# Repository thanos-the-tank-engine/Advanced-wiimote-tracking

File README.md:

# Advanced-wiimote-tracking
A python application for tracking nintendo wii controllers in 6 degrees of freedom

**This project is still very much a WIP. very little functionality has been implemented in it, and it is nowhere near completion at this time**

This application is designed to allow you to connect wii controllers to a computer and then channel the inputs from it into various emulated HID devices.
The goal of this software is to reduce the barrier of entry for 6DOF controller systems by enabling the use of a relatively low-cost system that can easily be DIY'd out of readily available objects. most current methods, such as the 3d-mouse style of controller, or the controllers used for a VR headset, are incredibly expensive. this software will allow you to accomplish the same thing using something that you probably have lying around already, or can buy secondhand for very little cost if you don't.

Included in this repository:  
\> Python scripts
\> KiCad project containing PCB layout and schematic for an improved sensor bar that expands on the capabilities of the Wii controller by enabling true 6DOF tracking.  
\> 3D model for the optional case of the improved sensor bar

Will be included in the future  
\> Firmware for improved sensor bar  
\> Maybe windows compatibility, if you windows-using plebians get lucky  

#Setup  
Right now, none of the setup process is automated. this means you will have to do it all yourself.
You will need to install my modified version of the Cwiid library that has support for the balance board added to it.
you will have to compile it yourself. I have not bothered trying to run this outside of my IDE because none of the UI exists yet.
If you want to use this on its own, good luck with that. either wait until it's finished or finish it yourself.

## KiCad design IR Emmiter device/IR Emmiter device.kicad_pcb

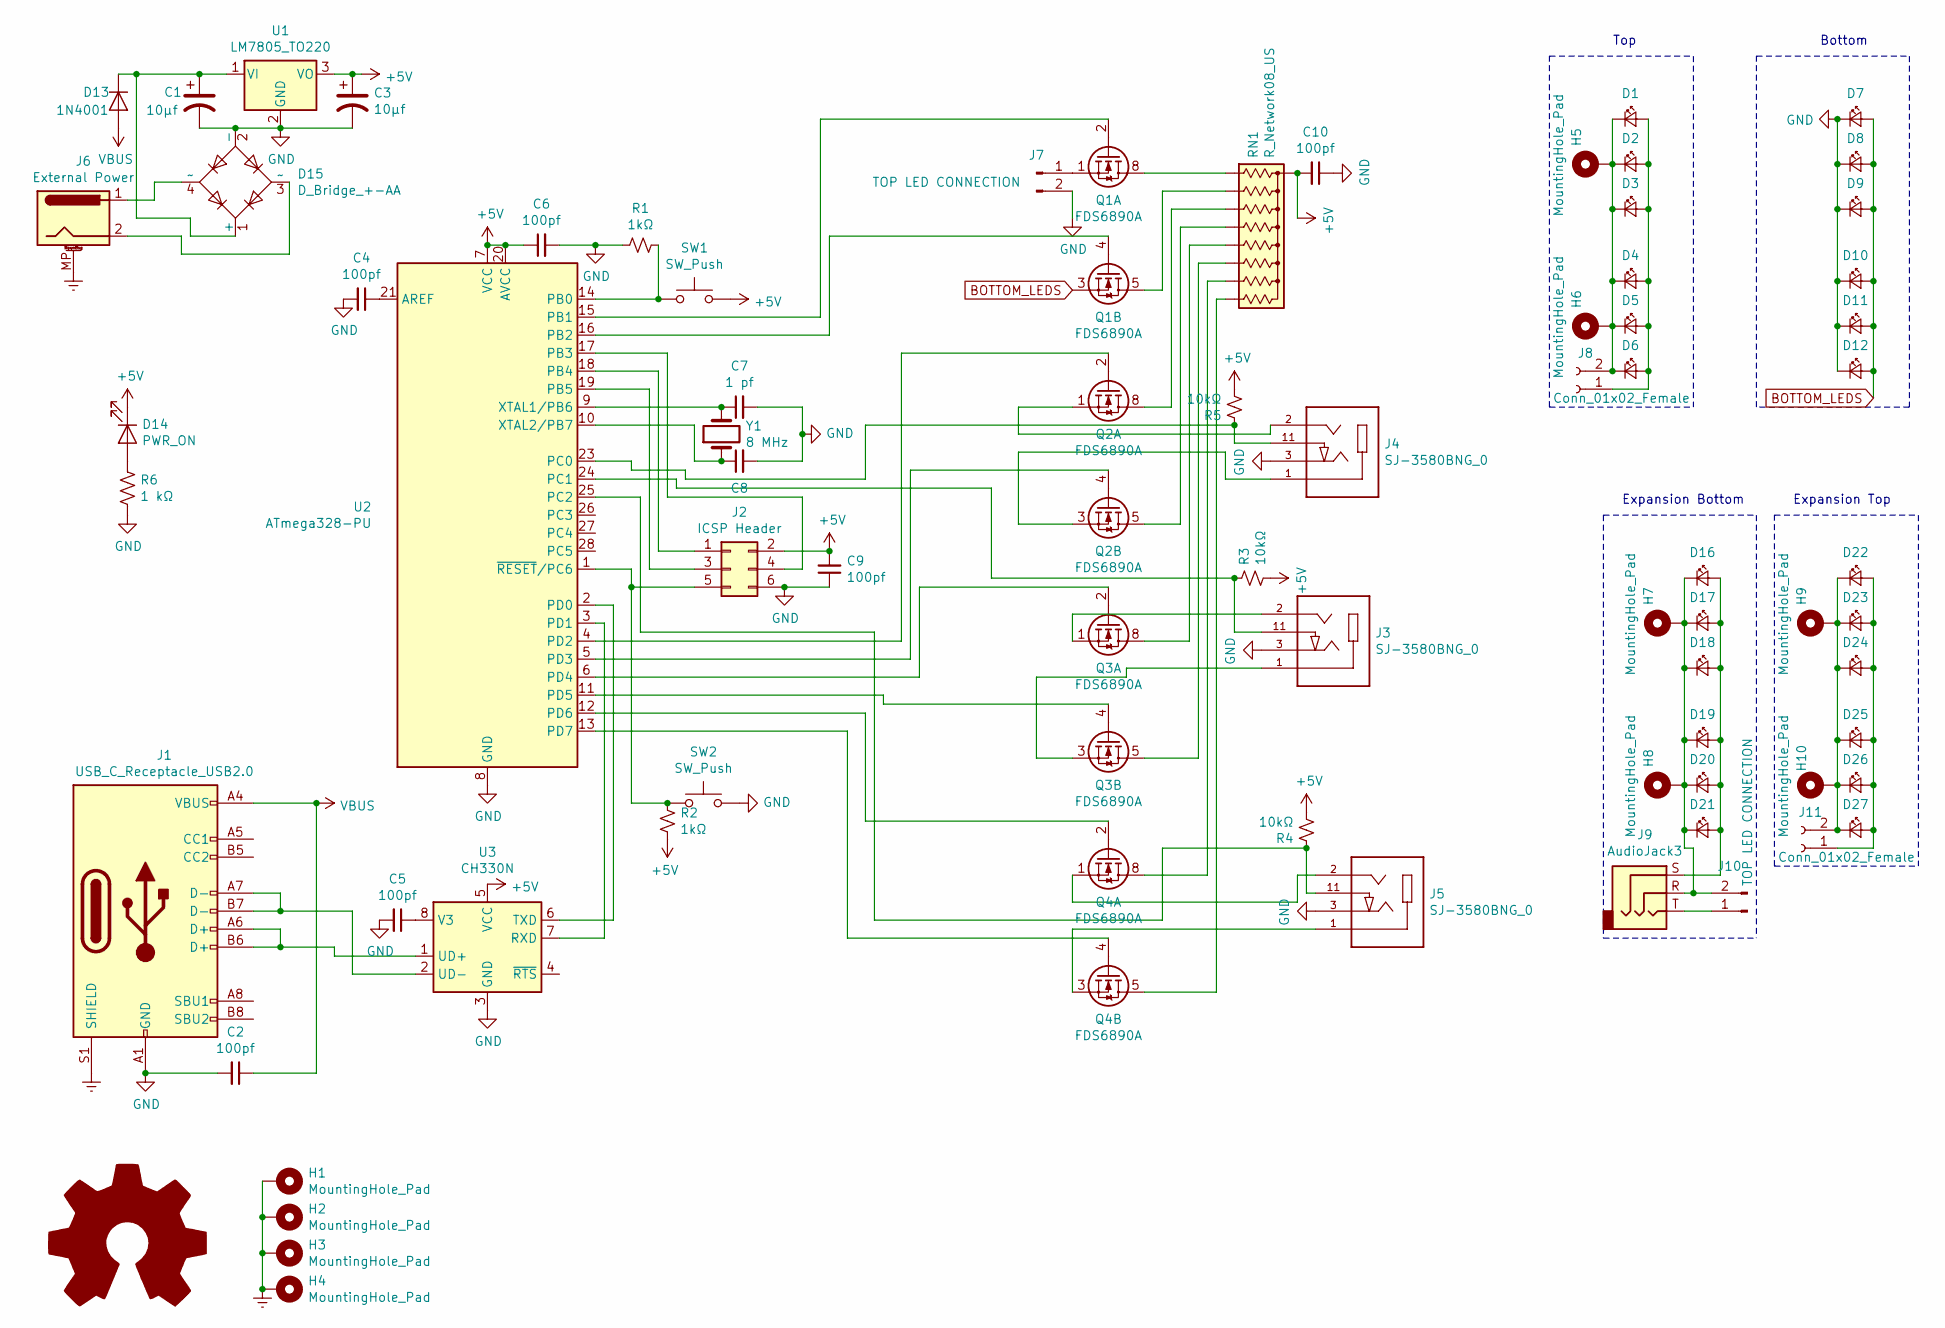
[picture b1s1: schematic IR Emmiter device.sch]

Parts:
C1, C3: 10μf; CP_Radial_D8.0mm_P2.50mm
C2, C4, C5, C6, C9, C10: 100pf; C_Disc_D8.0mm_W5.0mm_P10.00mm
C7: 1 pf; C_Disc_D8.0mm_W5.0mm_P10.00mm
C8: 1pf; C_Disc_D8.0mm_W5.0mm_P10.00mm
D1, D2, D3, D4, D5, D6, D7, D8, D9, D10, D11, D12, D16, D17, D18, D19, D20, D21, D22, D23, D24, D25, D26, D27: LED_Small; LED_D5.0mm_Horizontal_O1.27mm_Z3.0mm_Clear
D13: 1N4001; D_DO-41_SOD81_P10.16mm_Horizontal
D14: PWR_ON; LED_D5.0mm_Horizontal_O1.27mm_Z3.0mm
D15: D_Bridge_+-AA; Diode_Bridge_DIP-4_W5.08mm_P2.54mm
H1, H2, H3, H4, H5, H6, H7, H8, H9, H10: MountingHole_Pad; MountingHole_2.5mm_Pad_Via
J1: USB_C_Receptacle_USB2.0; USB4085-GF-A_REVA
J2: ICSP Header; PinHeader_2x03_P2.54mm_Vertical
J3, J4, J5: SJ-3580BNG_0; SJ-3580BNG
J6: External Power; BarrelJack_Horizontal
J7, J10: TOP LED CONNECTION; PinHeader_1x02_P2.54mm_Vertical
J8, J11: Conn_01x02_Female; PinSocket_1x02_P2.54mm_Vertical
J9: AudioJack3; Jack_3.5mm_CUI_SJ1-3533NG_Horizontal
LOGO1: Logo_Open_Hardware_Large; OSHW-Logo_5.7x6mm_SilkScreen
Q1, Q2, Q3, Q4: FDS6890A; SOIC-8_3.9x4.9mm_P1.27mm
R1, R2: 1kΩ; R_Axial_DIN0204_L3.6mm_D1.6mm_P7.62mm_Horizontal
R3, R4, R5: 10kΩ; R_Axial_DIN0204_L3.6mm_D1.6mm_P7.62mm_Horizontal
R6: 1 kΩ; R_Axial_DIN0204_L3.6mm_D1.6mm_P7.62mm_Horizontal
RN1: R_Network08_US; R_Array_SIP9
SW1, SW2: SW_Push; SW_PUSH_6mm
U1: LM7805_TO220; TO-220-3_Horizontal_TabDown
U2: ATmega328-PU; DIP-28_W7.62mm
U3: CH330N; SSOP-8_3.9x5.05mm_P1.27mm
Y1: 8 MHz; Crystal_HC49-4H_Vertical

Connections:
+5V: C3.1, C6.1, C9.2, C10.2, D14.1 (K), J2.2, R2.2, R3.1, R4.1, R5.1, RN1.1 (common), SW1.2, U1.3 (VO), U2.7 (VCC), U2.20 (AVCC), U3.5 (VCC)
BOTTOM_LEDS: D7.2 (A), D8.2 (A), D9.2 (A), D10.2 (A), D11.2 (A), D12.2 (A), Q1.3 (S2)
Earth: H1.1, H2.1, H3.1, H4.1, J1.P1, J1.P2, J1.P3, J1.P4, J1.S1 (SHIELD), J6.MP (MountPin)
GND: C1.2, C2.2, C3.2, C4.2, C5.2, C6.2, C7.2, C8.2, C9.1, C10.1, D7.1 (K), D8.1 (K), D9.1 (K), D10.1 (K), D11.1 (K), D12.1 (K), D15.2 (-), J1.A1 (GND), J1.A12 (GND), J1.B1 (GND), J1.B12 (GND), J2.6, J3.3, J4.3, J5.3, J7.2, R1.1, R6.2, SW2.2, U1.2 (GND), U2.8 (GND), U2.22 (GND), U3.3 (GND)
unnamed: C1.1, D13.1 (K), D15.1 (+), U1.1 (VI)
unnamed: C4.1, U2.21 (AREF)
unnamed: C5.1, U3.8 (V3)
unnamed: C7.1, U2.9 (XTAL1/PB6), Y1.2
unnamed: C8.1, U2.10 (XTAL2/PB7), Y1.1
unnamed: D1.1 (K), D2.1 (K), D3.1 (K), D4.1 (K), D5.1 (K), D6.1 (K), H5.1, H6.1, J8.2
unnamed: D1.2 (A), D2.2 (A), D3.2 (A), D4.2 (A), D5.2 (A), D6.2 (A), J8.1
unnamed: D14.2 (A), R6.1
unnamed: D15.3 (~~), J6.2
unnamed: D15.4 (~~), J6.1
unnamed: D16.1 (K), D17.1 (K), D18.1 (K), D19.1 (K), D20.1 (K), D21.1 (K), H7.1, H8.1, J9.R, J10.2
unnamed: D16.2 (A), D17.2 (A), D18.2 (A), D19.2 (A), D20.2 (A), D21.2 (A), J9.S
unnamed: D22.1 (K), D23.1 (K), D24.1 (K), D25.1 (K), D26.1 (K), D27.1 (K), H9.1, H10.1, J11.2
unnamed: D22.2 (A), D23.2 (A), D24.2 (A), D25.2 (A), D26.2 (A), D27.2 (A), J11.1
unnamed: J1.A6 (D+), J1.B6 (D+), U3.1 (UD+)
unnamed: J1.A7 (D-), J1.B7 (D-), U3.2 (UD-)
unnamed: J2.1, U2.18 (PB4)
unnamed: J2.3, U2.19 (PB5)
unnamed: J2.4, U2.17 (PB3)
unnamed: J2.5, R2.1, SW2.1, U2.1 (~RESET~/PC6)
unnamed: J3.1, Q3.3 (S2)
unnamed: J3.2, Q3.1 (S1)
unnamed: J3.11, R3.2, U2.24 (PC1)
unnamed: J4.1, Q2.3 (S2)
unnamed: J4.2, Q2.1 (S1)
unnamed: J4.11, R5.2, U2.23 (PC0)
unnamed: J5.1, Q4.3 (S2)
unnamed: J5.2, Q4.1 (S1)
unnamed: J5.11, R4.2, U2.25 (PC2)
unnamed: J7.1, Q1.1 (S1)
unnamed: J9.T, J10.1
unnamed: Q1.2 (G1), U2.15 (PB1)
unnamed: Q1.4 (G2), U2.16 (PB2)
unnamed: Q1.5 (D2), Q1.6 (D2), RN1.3 (R2)
unnamed: Q1.7 (D1), Q1.8 (D1), RN1.2 (R1)
unnamed: Q2.2 (G1), U2.4 (PD2)
unnamed: Q2.4 (G2), U2.5 (PD3)
unnamed: Q2.5 (D2), Q2.6 (D2), RN1.5 (R4)
unnamed: Q2.7 (D1), Q2.8 (D1), RN1.4 (R3)
unnamed: Q3.2 (G1), U2.6 (PD4)
unnamed: Q3.4 (G2), U2.11 (PD5)
unnamed: Q3.5 (D2), Q3.6 (D2), RN1.7 (R6)
unnamed: Q3.7 (D1), Q3.8 (D1), RN1.6 (R5)
unnamed: Q4.2 (G1), U2.12 (PD6)
unnamed: Q4.4 (G2), U2.13 (PD7)
unnamed: Q4.5 (D2), Q4.6 (D2), RN1.9 (R8)
unnamed: Q4.7 (D1), Q4.8 (D1), RN1.8 (R7)
unnamed: R1.2, SW1.1, U2.14 (PB0)
unnamed: U2.2 (PD0), U3.6 (TXD)
unnamed: U2.3 (PD1), U3.7 (RXD)
VBUS: C2.1, D13.2 (A), J1.A4 (VBUS), J1.A9 (VBUS), J1.B4 (VBUS), J1.B9 (VBUS)

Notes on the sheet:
Top
Bottom
Expansion Top
Expansion Bottom

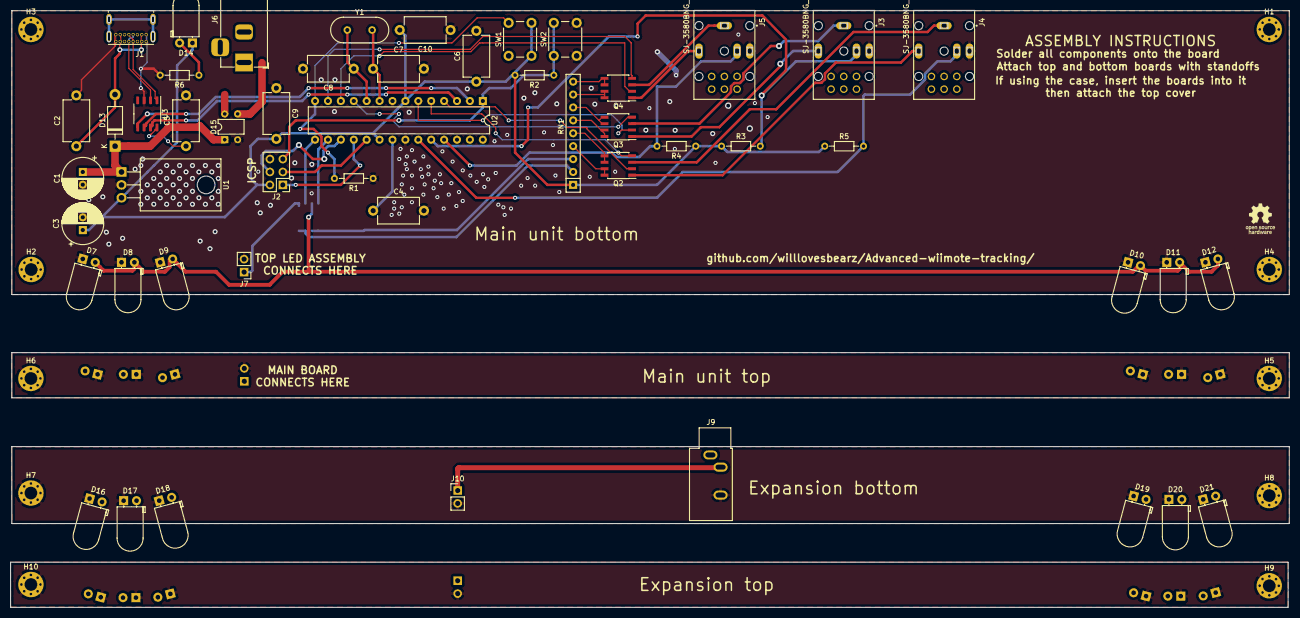
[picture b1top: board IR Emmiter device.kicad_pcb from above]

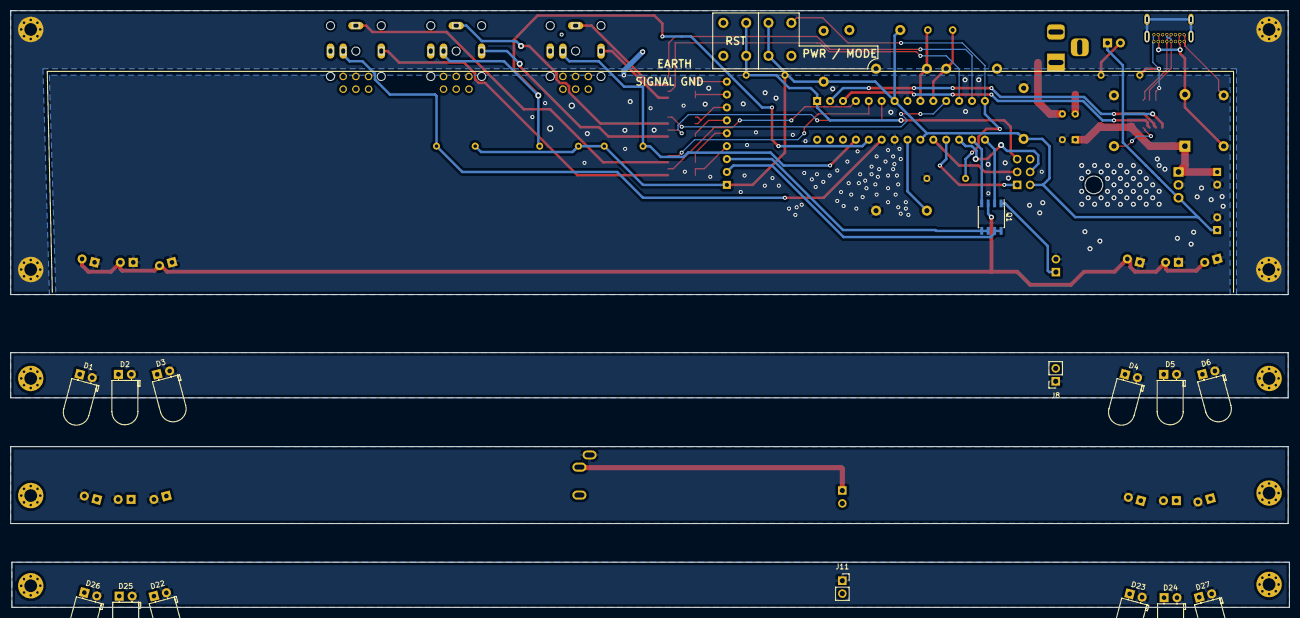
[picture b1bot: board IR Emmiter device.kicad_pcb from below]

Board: 2 copper layers, 251.7 x 117.5 mm, 76 parts (15 on the bottom side), 55 nets.

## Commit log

2019-10-22 Progress from 10-21-19
2019-10-22 Delete Plan.txt
    file no longer needed
2019-10-22 Update README.md
    Clarified the reason for creating this software
2019-10-22 Small cleanup
2019-10-22 More cleanup, added and improved comments, added more TODO statements.
2019-10-23 Added schematic and PCB design for advanced IR emitter
2019-10-23 Minor changes to schematic, swapped out parts on PCB layout to aid in case design and added footprints for the expansions
2019-10-24 Completed basic shape of case for main unit, finished layout of PCB for improved sensor bar
2019-10-28 Added function that handles accelerometer input properly, expanded upon some major TODOs, put framework in place for fixing the 3DOF tracker, fixed some aesthetic issues with indentation
2019-10-28 more aesthetic changes, grammar corrections, added button handling to joystick module
2019-10-28 Removed unnescesary file
2019-10-29 Fixed input scripts, minor cleanup
2019-10-29 Formatting changes for aesthetics, added comments, general cleanup and despaghettification
2019-10-29 Fixed Joystick input method, fixed formatting for aesthetics, re-worked comments
2019-10-30 Finalized trig-based 3DOF tracking method
2019-10-30 Fixed Mouse HID method not working
2019-10-30 Added function for handling MotionPlus module, minor performance optimizations
2019-10-31 Updated readme, started work on MotionPlus support for 3DOF tracker
2019-10-31 Added support for balance board, wrote input script to handle it as a joystick.
